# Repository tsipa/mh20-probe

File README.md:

# m&h 20.00 receiver

A DIY receiver for the **m&h 20.00 wireless touch probe**, built from an ESP32-WROOM DevKit, a 433 MHz CC1101 radio and a 240×240 IPS display. It scans 433–435 MHz, finds the probe, detects contact and drives two PhotoMOS outputs (READY and PROBE) for a SINUMERIK 828D.

## Status

- **Breadboard prototype (P3-era firmware): works on hardware.** It picks up the probe, detects contact and shows the state on the display. See the [UART log and bench check](evidence/working/).
- **P4 carrier PCB: designed, not built.** 98 x 70 mm, 2 layers, all parts on the top side, everything hand soldered (no sockets, because the machine vibrates). It passes KiCad DRC (with schematic parity) and ERC, but has not been fabricated or assembled.
- **P4 firmware changes** (first CONTACT frame no longer dropped, timer-based output guard, task watchdog) pass the host tests, but have not yet been compiled with arduino-cli or run on hardware.
- **SINUMERIK 828D input side: not verified on the machine.**

Details: [testing status](docs/validation.md).

## Device photos

The white button on the mushroom-shaped top activates the probe. The black button near the battery sweeps the radio channels. The probe uses a 9 V PP3 (Krona) battery. [More photos and controls](docs/probe-behavior.md#physical-probe-and-controls).

## Wi-Fi updates

The receiver can start **MH-Probe-Service**, join your router, or do both. Use the web page for status, Wi-Fi settings and firmware uploads; UART commands can change or reset the settings too. The service login is **admin**, with a password printed over USB serial. Once the probe is detected, Wi-Fi switches off until the receiver restarts. [Setup and updates](docs/wifi-update.md).

## Display

Display previews rendered with the firmware's fonts and colors. The readings are examples.

| Color | Meaning | READY | Probe loop |
|---|---|---:|---|
| Red | No validated messages / search / error | 0 | Open |
| Green | Valid probe, free | 1 | Closed |
| Blue | Contact | 1 | Open |

The display holds blue for at least 100 ms so brief contacts are visible. The outputs update as soon as a contact frame is accepted. If no valid messages arrive for 65 ms, READY goes low and the probe loop opens.

## Power and USB

The P4 carrier uses a **non-isolated** DD4012SA 5 V buck module: machine 0 V is the logic GND. Only the two PhotoMOS output contacts are isolated. **With JP1 fitted, do not connect USB to a PC while the board is on machine 24 V.** Remove JP1 to power the board from USB on the bench. See [power](docs/power.md).

## Documentation

- [P4 carrier PCB](hardware/pcb/README.md): KiCad project, schematic, [BOM](hardware/pcb/bom.csv), Gerbers (`hardware/pcb/fab`), 1:1 prints (`hardware/pcb/print`) and check reports.
- [ESP32, CC1101 and LCD wiring](docs/wiring.md): pin tables and diagram.
- [Radio protocol](docs/protocol.md): FREE/CONTACT pulses, validation and acquisition.
- [Probe behavior](docs/probe-behavior.md): battery, buttons, channel sweep, activation and contact.
- [Wi-Fi and OTA updates](docs/wifi-update.md): service network, browser uploads and restart.
- [Build and upload](docs/build.md): Arduino IDE/CLI and dependency versions.
- [24 V power](docs/power.md) and [SINUMERIK 828D outputs](docs/machine-interface.md).
- [Testing status](docs/validation.md), [recorded test signals](fixtures/README.md).
- [Component references](hardware/pcb/components/README.md): specifications, pinouts, dimensions and drawings.

## Source and test data

- [Arduino sketch](firmware/probe_rx/probe_rx.ino): receiver firmware.
- [Protocol parameters JSON](protocol/probe.json), [wiring JSON](hardware/wiring.json).
- [Reference Python DSP](protocol/reference/): recording acquisition and demodulation.
- [Bench check](evidence/working/receiver-check.json).

## Run the tests

```powershell
python -m venv .venv
.\.venv\Scripts\python.exe -m pip install -r requirements-dev.txt
.\.venv\Scripts\python.exe scripts\test.py
```

Tests run on the computer without an ESP32 or SDR connected. The display test needs the Adafruit GFX 1.13.0 source; use `--gfx` to specify its location if it is not found automatically.

The full radio recordings are not included. The repository contains short excerpts for testing, with checksums.

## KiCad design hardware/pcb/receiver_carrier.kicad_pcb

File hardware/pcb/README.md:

# MH20 receiver carrier PCB (P4)

Carrier board for the receiver: an ESP32 DevKitC, an Ebyte E07 CC1101 433 MHz radio, a 1.3 in ST7789 LCD, a 24 V to 5 V buck module and two AQY212EH PhotoMOS relays that switch the machine's PROBE and READY inputs.

P4 replaces P3 (110 x 100 mm, isolated DC/DC module, ESP32 on the back side). P4 is designed and checked but not fabricated yet.

## Board

- 98 x 70 mm, 2 layers, 1.6 mm, four M3 corner holes (H1-H4).
- All parts on the top side, all through-hole and soldered by hand. The modules are soldered through male pin headers directly into the carrier; there are no sockets, because the machine vibrates.
- Routed by hand (routes are in `p4/spec.json`), one via, no copper pours. Track widths: signal 0.4 mm, power 0.8 mm, isolated outputs 0.6 mm.

## Layout (top view)

| Ref | Part | Position |
|---|---|---|
| J2 | LCD ER-TFTM013-1 | Left, rotated 180 degrees, header at the bottom. `firmware/probe_rx/DisplayPanel.h` uses rotation 0 for this placement |
| A1 | ESP32 DevKitC V4, 38 pins, rows 25.40 mm apart | Centre; pin 1 top left, WROOM antenna over the top edge (no copper below it), USB connector pointing down |
| JP1 | 1x2 header + jumper cap | Below the ESP32 |
| J3 | Ebyte E07-M1101D-SMA | Top right, SMA jack over the top edge |
| R1, K1 | PROBE output | Right middle |
| R2, K2 | READY output | Right middle, below K1 |
| U1 | DD4012SA 5 V buck | Bottom right |
| J1 | 6-pole screw terminal | Right edge, wire entry off the board, pin 1 at the bottom |

The USB plug area below the ESP32 (12 x 25 mm) is kept free of tall parts.

## Connections

| Connector | Pins |
|---|---|
| J1 machine, 5.08 mm | 1 = 24V_IN, 2 = 0V/GND, 3 = READY_A, 4 = READY_B, 5 = PROBE_A, 6 = PROBE_B |
| J2 LCD | 1 = GND, 2 = 3V3, 3 = SCK/GPIO14, 4 = MOSI/GPIO13, 5 = RST/GPIO27, 6 = DC/GPIO32, 7 = BLK/3V3 |
| J3 radio | 1 = GND, 2 = 3V3, 3 = GDO0/GPIO26, 4 = CSN/GPIO5, 5 = SCK/GPIO18, 6 = MOSI/GPIO23, 7 = MISO/GPIO19, 8 = GDO2 not connected |
| JP1 | 1 = 5V_REG (U1 OUT), 2 = 5V_DEV (ESP32 5V pin) |

The full netlist is `p4/netlist.json`.

## Power

24V_IN (J1.1) feeds U1 IN. U1 OUT (5V_REG) goes through JP1 to the ESP32 5V pin (5V_DEV). The ESP32 board's own regulator supplies 3V3 to the LCD and the radio. **Remove JP1 before connecting USB.**

U1 is a 3-pin 7805-pinout buck module (IN, GND, OUT at 2.54 mm), input 4.75-40 V; the silkscreen limits the supply to 36 V. It is **not isolated**: machine 0 V (J1.2) is logic GND, so a PC on the USB port is also tied to machine 0 V. Only the PhotoMOS outputs are isolated.

## Relay outputs

K1 closes PROBE_A/B while GPIO25 is HIGH; K2 closes READY_A/B while GPIO33 is HIGH. Each GPIO drives its relay LED through a 150 ohm resistor; the LED cathodes return to GND. The outputs are floating and bidirectional, so either pin of a pair may go to the positive side. Firmware sets both GPIOs LOW before enabling them as outputs. READY is closed while the probe link is valid; PROBE is closed only while the linked probe is free, so touch or link loss opens it. GPIO state during reset is not guaranteed; this is not a safety circuit. Machine-side wiring: [docs/machine-interface.md](../../docs/machine-interface.md).

LED current with 150 ohm 1%: at least (2.64 V - 1.5 V) / 151.5 ohm = 7.5 mA (minimum GPIO HIGH, maximum VF), about 14 mA typical at 3.3 V with VF 1.14 V. Even with VF = 0 the current stays below 23 mA and the resistor dissipation below 0.08 W.

AQY212EH: 60 V load voltage, 0.55 A at 25 C, on resistance up to 2.5 ohm, off leakage up to 1 uA, turn-on up to 4 ms and turn-off up to 1 ms at IF = 5 mA, 25 C. 1 ms corresponds to 0.01 mm travel at 600 mm/min.

Isolated output nets (PROBE_A/B, READY_A/B) keep 3.0 mm to all other copper and 0.8 mm to each other. Exceptions are pad pairs inside K1/K2 and J1: the MKDS footprint has 2.6 mm pads at 5.08 mm pitch, so J1.2 (GND) to J1.3 (READY_A) is 2.48 mm. 24V_IN keeps 0.8 mm to logic signals and 5 mm from the radio.

## Mounting hardware

| Item | Carrier hole | Screw |
|---|---|---|
| Board H1-H4 | 3.2 mm, no copper within 4.0 mm | M3 |
| LCD (module holes 2.0 mm) | four 2.2 mm holes | M1.6 with insulating spacers |
| Radio | two 3.2 x 5.2 mm slots, cover the 28 mm and 30 mm module versions | M2.5 with insulating spacers |

Spacer height equals the standoff of the soldered header; measure it on the actual module.

## Part choices

- **DD4012SA buck (U1).** Three pins in the 7805 pinout, 12 x 14 mm, wide input range for a 24 V machine supply. The isolated DC/DC module was dropped for size and part count, since the machine-facing contacts are already isolated by the PhotoMOS relays. Any 7805-pinout 5 V module rated for at least 30 V input fits the footprint.
- **AQY212EH with 150 ohm (K1/K2, R1/R2).** DIP-4 PhotoMOS with a floating bidirectional 60 V output and low leakage, suitable for a 24 V machine input of either polarity. 150 ohm keeps the LED current above the 5 mA datasheet timing condition with margin; turn-on time drops with higher LED current. Do not substitute the surface-mount AQY212EHA.
- **Phoenix MKDS 1,5/6-5,08 (J1).** 6 poles, 5.08 mm pitch, 1.3 mm pins. Any 5.08 mm 6-pole terminal with the same pin size and body fits; KF301 types with 5.0 mm pitch do not.

## Files

| Path | Content |
|---|---|
| `p4/spec.json` | Placement, routes, vias, silkscreen (source) |
| `p4/netlist.json` | Nets, no-connect pins, net classes, footprints (source) |
| `receiver_carrier.kicad_sch`, `Carrier.kicad_sym`, `sym-lib-table` | Schematic and symbols; the first two are generated by `tools/schematic.py` |
| `receiver_carrier.kicad_pcb`, `.kicad_pro`, `.kicad_dru`, `fp-lib-table` | KiCad project, generated by `p4.py build` |
| `Carrier.pretty/` | Footprints, generated by `tools/footprints.py` |
| `bom.csv` | Bill of materials |
| `fab/` | Gerbers, Excellon drills (PTH and NPTH with slots), drill maps, job file |
| `print/` | 1:1 PDFs: front, mirrored back, combined print with 50 mm calibration bars; `receiver_carrier-schematic.pdf` |
| `preview/` | PNG previews (front assembly, back, F.Cu, B.Cu) |
| `check/` | Last check: `report.txt`, KiCad DRC, extra checks, geometry, schematic netlist |
| `sources/` | Datasheets and module drawings |
| [components/](components/README.md) | Dimensions, pinouts and drawings per part |
| [tools/](tools/README.md) | Build, check, export and render tools |

## Build and check

```
python -I hardware/pcb/tools/schematic.py
python -I hardware/pcb/tools/p4.py build  hardware/pcb/p4/spec.json --out hardware/pcb
python -I hardware/pcb/tools/p4.py check  hardware/pcb/p4/spec.json --out hardware/pcb
python -I hardware/pcb/tools/p4.py export hardware/pcb/p4/spec.json --out hardware/pcb
python -I hardware/pcb/tools/p4.py render hardware/pcb/p4/spec.json --out hardware/pcb
```

Last result (KiCad 10.0.8): DRC 0 items with schematic parity, extra checks 0 violations, schematic ERC 0. ERC uses passive pins and does not validate the module internals.

## Before soldering

Print `print/receiver_carrier-print-1to1.pdf` at 100% / actual size with page fitting disabled; the calibration bars must measure 50 mm. Lay the actual ESP32, LCD, radio, buck module and terminal on the print and check pin 1, header positions, support holes, SMA and USB clearance.

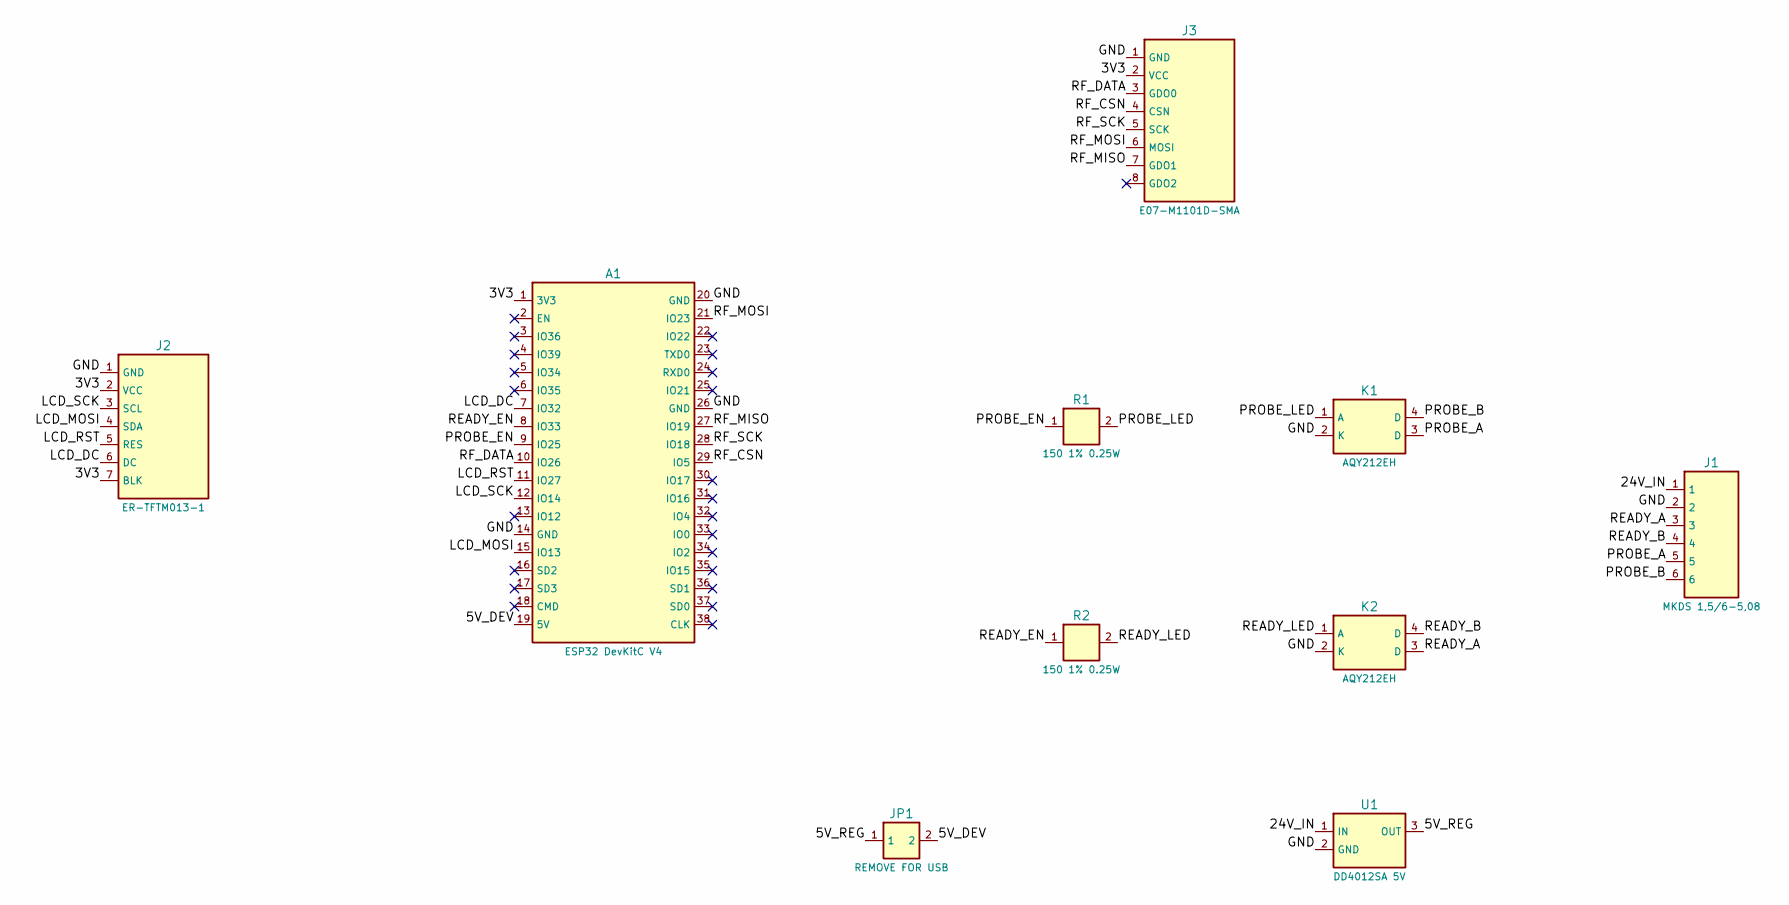
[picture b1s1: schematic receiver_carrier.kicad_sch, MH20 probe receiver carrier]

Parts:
A1: ESP32 DevKitC V4; esp32
J1: MKDS 1,5/6-5,08; TerminalBlock_Phoenix_MKDS-1,5-6-5.08_1x06_P5.08mm_Horizont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
J2: ER-TFTM013-1; lcd
J3: E07-M1101D-SMA; radio_e07
JP1: REMOVE FOR USB; PinHeader_1x02_P2.54mm_Vertical
K1, K2: AQY212EH; DIP-4_W7.62mm
R1, R2: 150 1% 0.25W; R_Axial_DIN0207_L6.3mm_D2.5mm_P7.62mm_Horizontal
U1: DD4012SA 5V; Buck_SIP3_7805

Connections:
/3V3: A1.1 (3V3), J2.2 (VCC), J2.7 (BLK), J3.2 (VCC)
/5V_DEV: A1.19 (5V), JP1.2
/5V_REG: JP1.1, U1.3 (OUT)
/24V_IN: J1.1, U1.1 (IN)
/GND: A1.14 (GND), A1.20 (GND), A1.26 (GND), J1.2, J2.1 (GND), J3.1 (GND), K1.2 (K), K2.2 (K), U1.2 (GND)
/LCD_DC: A1.7 (IO32), J2.6 (DC)
/LCD_MOSI: A1.15 (IO13), J2.4 (SDA)
/LCD_RST: A1.11 (IO27), J2.5 (RES)
/LCD_SCK: A1.12 (IO14), J2.3 (SCL)
/PROBE_A: J1.5, K1.3 (D)
/PROBE_B: J1.6, K1.4 (D)
/PROBE_EN: A1.9 (IO25), R1.1
/PROBE_LED: K1.1 (A), R1.2
/READY_A: J1.3, K2.3 (D)
/READY_B: J1.4, K2.4 (D)
/READY_EN: A1.8 (IO33), R2.1
/READY_LED: K2.1 (A), R2.2
/RF_CSN: A1.29 (IO5), J3.4 (CSN)
/RF_DATA: A1.10 (IO26), J3.3 (GDO0)
/RF_MISO: A1.27 (IO19), J3.7 (GDO1)
/RF_MOSI: A1.21 (IO23), J3.6 (MOSI)
/RF_SCK: A1.28 (IO18), J3.5 (SCK)

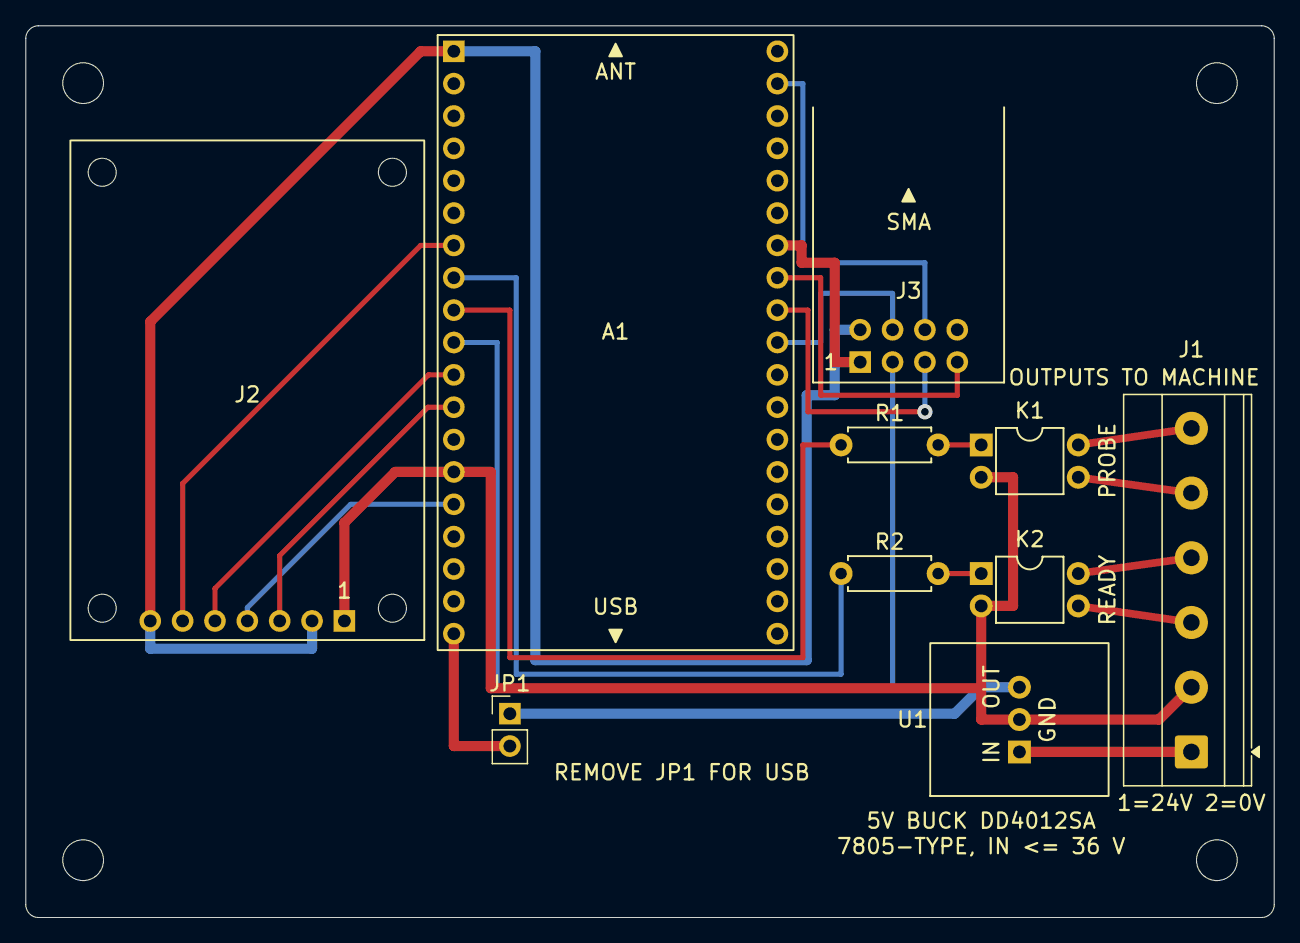
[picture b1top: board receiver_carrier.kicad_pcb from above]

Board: 2 copper layers, 98.0 x 70.0 mm, 14 parts (0 on the bottom side), 22 nets.

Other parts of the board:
H1, H2, H3, H4: M3; Mount_M3
